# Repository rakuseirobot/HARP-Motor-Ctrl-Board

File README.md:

# HARP-Motor-Ctrl-Board
Board for controlling motor.

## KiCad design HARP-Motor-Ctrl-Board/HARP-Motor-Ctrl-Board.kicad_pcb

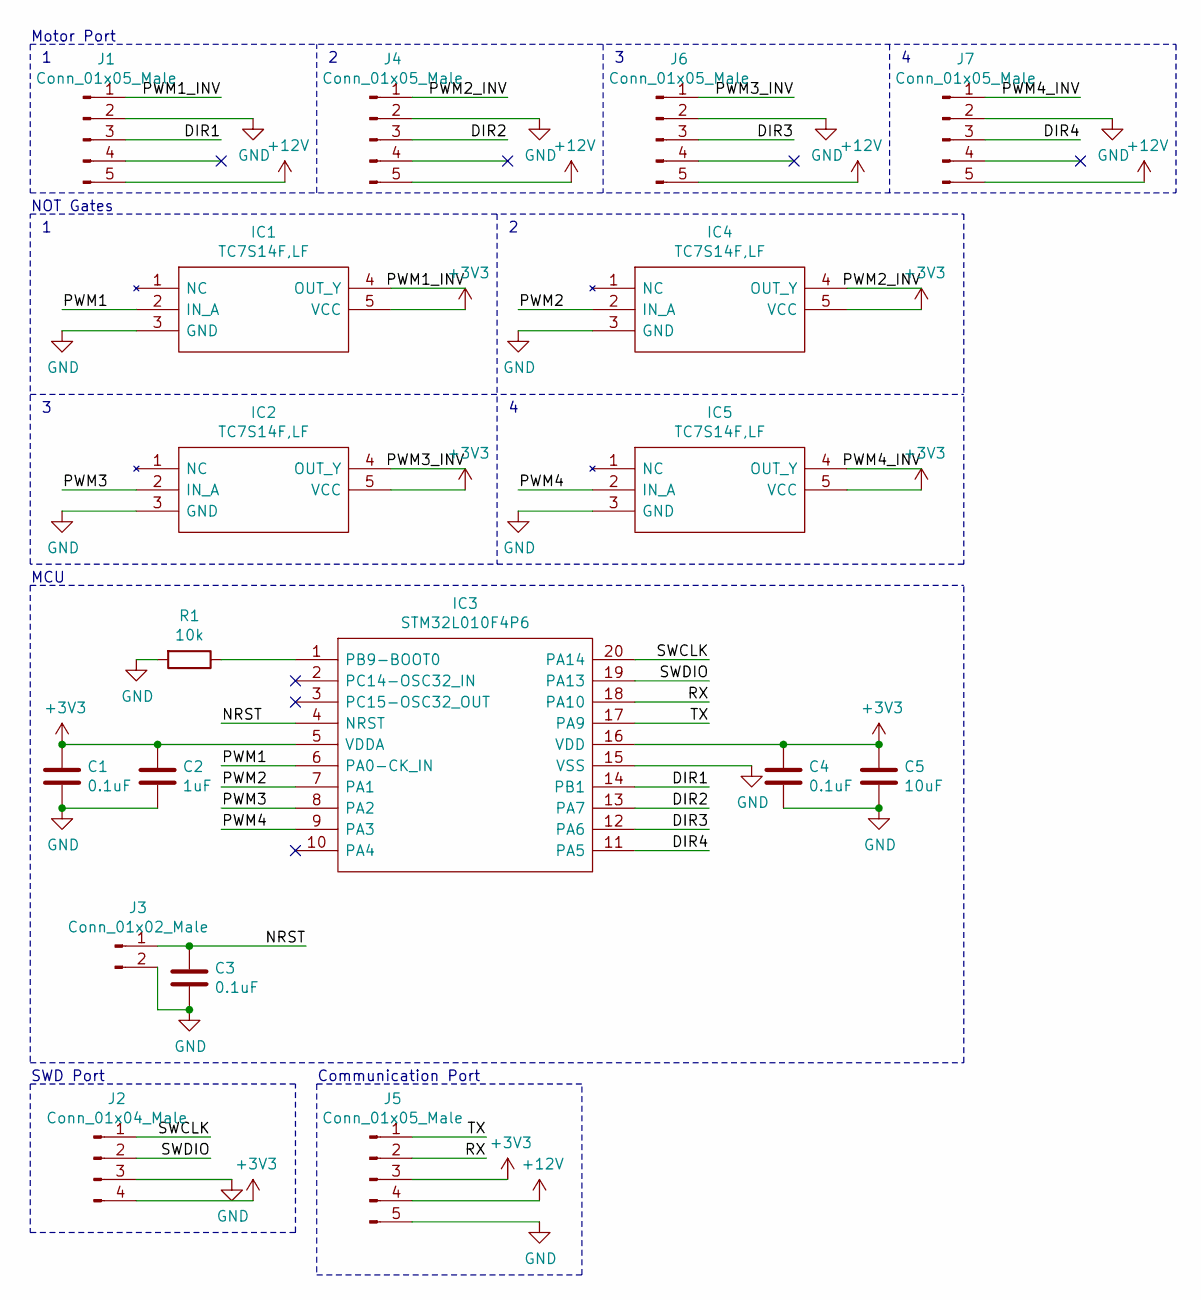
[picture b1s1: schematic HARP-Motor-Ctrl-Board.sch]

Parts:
C1, C3, C4: 0.1uF; C_0603_1608Metric_Pad1.05x0.95mm_HandSolder
C2: 1uF; C_0603_1608Metric_Pad1.05x0.95mm_HandSolder
C5: 10uF; C_0603_1608Metric_Pad1.05x0.95mm_HandSolder
IC1, IC2, IC4, IC5: TC7S14F,LF; SOT95P275X140-5N; Manufacturer_Part_Number TC7S14F,LF; Mouser Part Number 757-TC7S14FLF
IC3: STM32L010F4P6; SOP65P640X120-20N; Manufacturer_Part_Number STM32L010F4P6; Mouser Part Number 511-STM32L010F4P6
J1, J4, J6, J7: Conn_01x05_Male; JST_PH_B5B-PH-K_1x05_P2.00mm_Vertical
J2: Conn_01x04_Male; JST_XH_B4B-XH-A_1x04_P2.50mm_Vertical
J3: Conn_01x02_Male; PinHeader_1x02_P2.54mm_Vertical
J5: Conn_01x05_Male; JST_XH_B5B-XH-A_1x05_P2.50mm_Vertical
R1: 10k; R_0603_1608Metric

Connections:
+3V3: C1.1, C2.1, C4.1, C5.1, IC1.5 (VCC), IC2.5 (VCC), IC3.5 (VDDA), IC3.16 (VDD), IC4.5 (VCC), IC5.5 (VCC), J2.4, J5.3
+12V: J1.5, J4.5, J5.4, J6.5, J7.5
/DIR1: IC3.14 (PB1), J1.3
/DIR2: IC3.13 (PA7), J4.3
/DIR3: IC3.12 (PA6), J6.3
/DIR4: IC3.11 (PA5), J7.3
/NRST: C3.1, IC3.4 (NRST), J3.1
/PWM1: IC1.2 (IN_A), IC3.6 (PA0-CK_IN)
/PWM1_INV: IC1.4 (OUT_Y), J1.1
/PWM2: IC3.7 (PA1), IC4.2 (IN_A)
/PWM2_INV: IC4.4 (OUT_Y), J4.1
/PWM3: IC2.2 (IN_A), IC3.8 (PA2)
/PWM3_INV: IC2.4 (OUT_Y), J6.1
/PWM4: IC3.9 (PA3), IC5.2 (IN_A)
/PWM4_INV: IC5.4 (OUT_Y), J7.1
/RX: IC3.18 (PA10), J5.2
/SWCLK: IC3.20 (PA14), J2.1
/SWDIO: IC3.19 (PA13), J2.2
/TX: IC3.17 (PA9), J5.1
GND: C1.2, C2.2, C3.2, C4.2, C5.2, IC1.3 (GND), IC2.3 (GND), IC3.15 (VSS), IC4.3 (GND), IC5.3 (GND), J1.2, J2.3, J3.2, J4.2, J5.5, J6.2, J7.2, R1.2
unnamed: IC3.1 (PB9-BOOT0), R1.1

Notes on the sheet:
Motor Port
NOT Gates
MCU
SWD Port
Communication Port

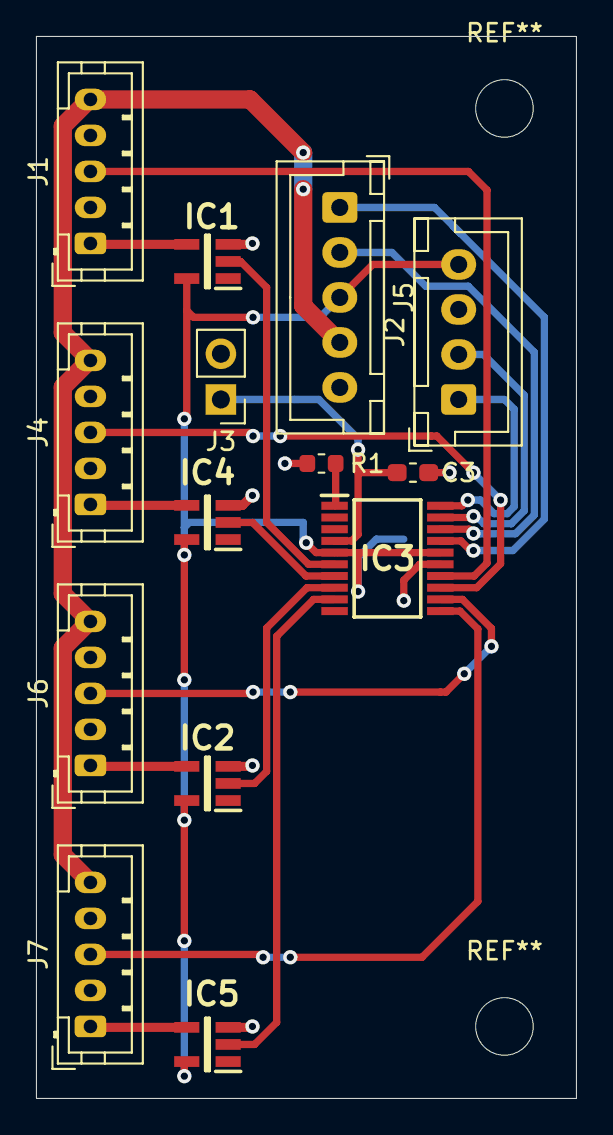
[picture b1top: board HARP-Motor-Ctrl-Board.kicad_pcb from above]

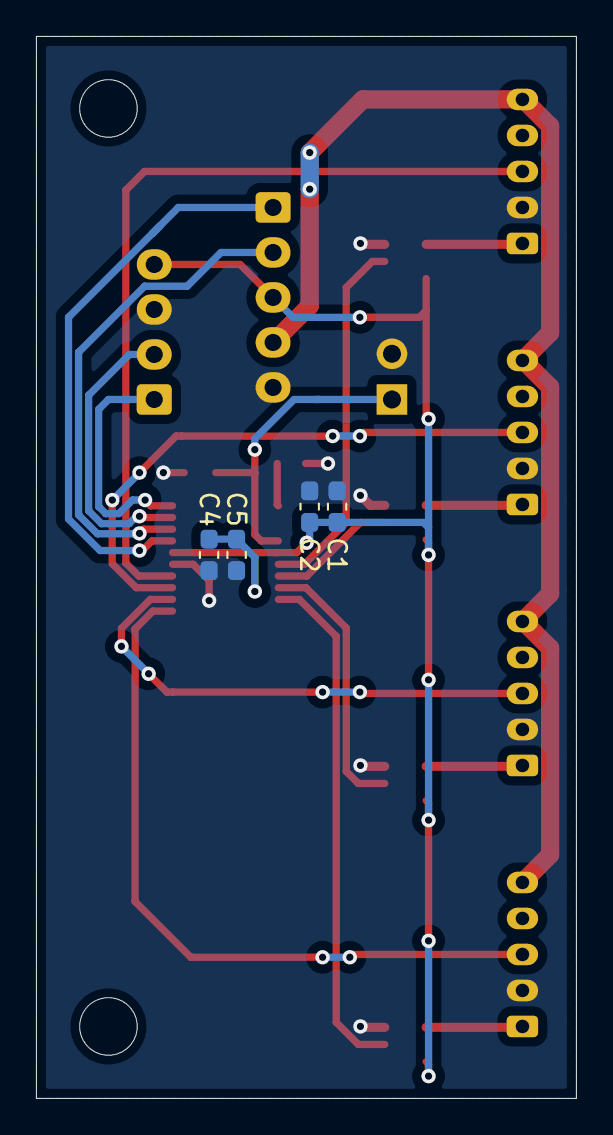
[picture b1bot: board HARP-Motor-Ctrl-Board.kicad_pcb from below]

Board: 2 copper layers, 30.0 x 59.0 mm, 18 parts (4 on the bottom side), 21 nets.

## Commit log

2020-11-23 designing all done and there's no error reported by ERC and/or DRC.
2020-11-23 Generate gerber file and zipped them.
2020-11-23 added logo and regenerated gerber files.
